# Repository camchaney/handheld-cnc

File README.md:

## Description
Compass is a DIY handheld CNC router designed to make CNC machining more accessible.

Unlike traditional CNC machines that move a cutting tool within a fixed workspace, Compass relies on users to guide the device around the workpiece directly. It automatically adjusts the cutting tool to stay on the programmed design path, enabling a significantly smaller device footprint while still handling large-scale cuts.

This is all accomplished using optical flow mouse sensors to track the position of the device, as well as a belt driven coreXY gantry to adjust the tool. The brains are a Teensy 4.1 microcontroller.

## Getting Started
This repo contains all of the source to build a Handheld CNC Router: the firmware, CAD files for 3D printing/manufacturing, BOM, and cable diagrams.

### Navigation
Internal
- [main](main/) - main firmware (written for [PlatformIO](https://docs.platformio.org/en/latest/core/quickstart.html) usage)
- [cad](cad/) - custom hardware (3D prints, laser cut sheet metal, cable harnesses)
- [pcb](pcb/) - printed circuit board designs for motherboard and sensors
- [dev](dev/) - development folder for debugging and testing
- [examples](examples/) - example gcode files to test with your machine!

External
- [BOM](https://docs.google.com/spreadsheets/d/12QS1CGSAB-lqKIOotCXDaXmJv9cjfRvVEAgQbRd7MnY/edit?usp=sharing)
- [Assembly Instructions](https://drive.google.com/drive/folders/1fIALrTWUbJRqTl93RGrUaR8dMfO7AI_g?usp=sharing)

## Disclaimer
This project is a work-in-progress. Development is rapidly occurring, so design files and firmware may change.

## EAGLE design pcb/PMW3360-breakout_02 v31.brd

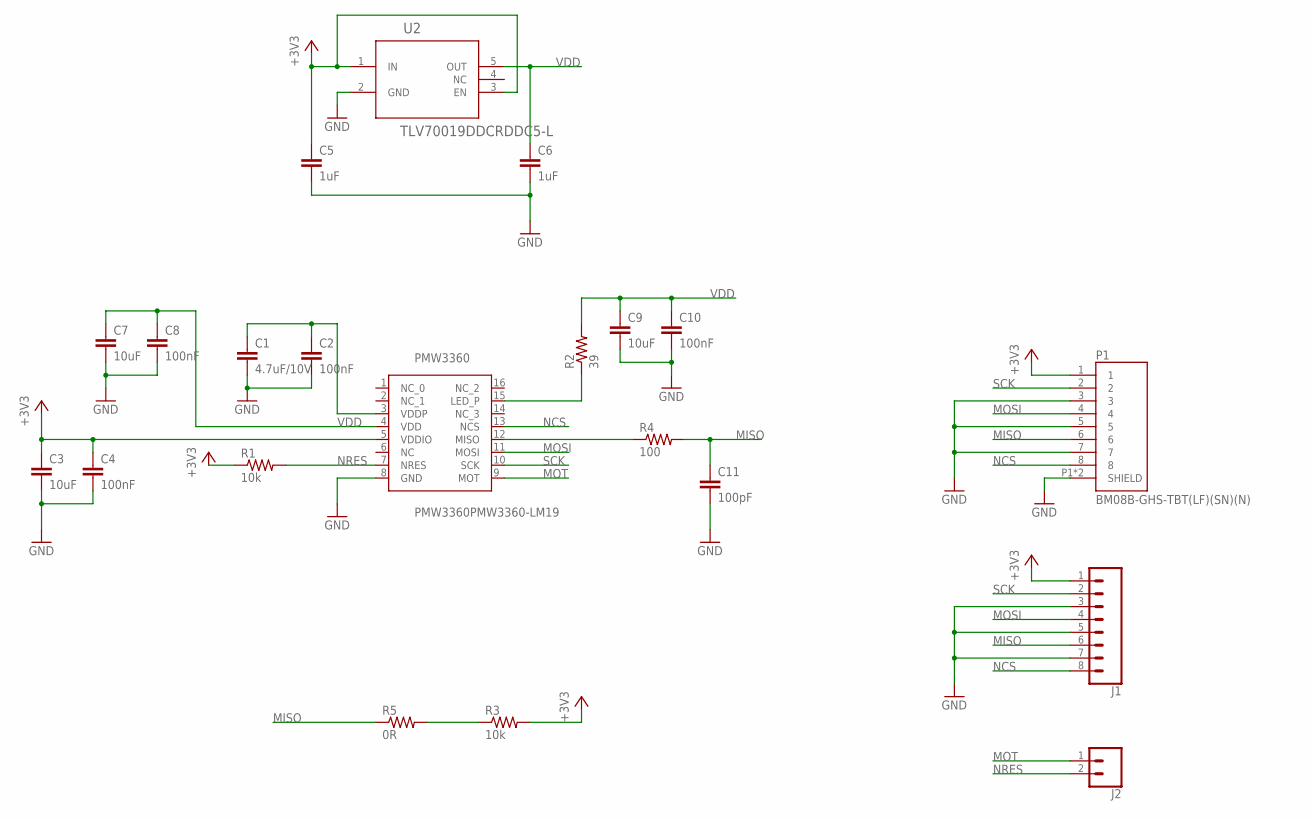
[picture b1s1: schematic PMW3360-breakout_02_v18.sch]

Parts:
C1: 4.7uF/10V; CAPC1608X85
C2, C4, C8, C10: 100nF; CAPC1005X60
C3, C7, C9: 10uF; CAPC1005X60
C5, C6: 1uF; CAPC1005X60
C11: 100pF; C0402K
J1: CONN_08"; 1X08
J2: CONN_02; 1X02
P1: BM08B-GHS-TBT(LF)(SN)(N); JST_BM08B-GHS-TBT(LF)(SN)(N)
PMW3360: PMW3360PMW3360-LM19; PMW3360
R1, R3: 10k; R0402
R2: 39; R0402
R4: 100; R0402
R5: 0R; R0402
U2: TLV70019DDCRDDC5-L; DDC5-L

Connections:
+3V3: C3.1, C4.1, C5.1, J1.1, P1.1, PMW3360.5 (VDDIO), R1.1, R3.2, U2.1 (IN), U2.3 (EN)
GND: C1.2, C2.2, C3.2, C4.2, C5.2, C6.2, C7.2, C8.2, C9.2, C10.2, C11.2, J1.3, J1.5, J1.7, P1.3, P1.5, P1.7, P1.P1 (SHIELD), P1.P2 (SHIELD), PMW3360.8 (GND), U2.2 (GND)
MISO: C11.1, J1.6, P1.6, R4.2, R5.1
MOSI: J1.4, P1.4, PMW3360.11 (MOSI)
MOT: J2.1, PMW3360.9 (MOT)
unnamed: PMW3360.15 (LED_P), R2.1
unnamed: C1.1, C2.1, PMW3360.3 (VDDP)
unnamed: PMW3360.12 (MISO), R4.1
unnamed: R3.1, R5.2
NCS: J1.8, P1.8, PMW3360.13 (NCS)
NRES: J2.2, PMW3360.7 (NRES), R1.2
SCK: J1.2, P1.2, PMW3360.10 (SCK)
VDD: C6.1, C7.1, C8.1, C9.1, C10.1, PMW3360.4 (VDD), R2.2, U2.5 (OUT)

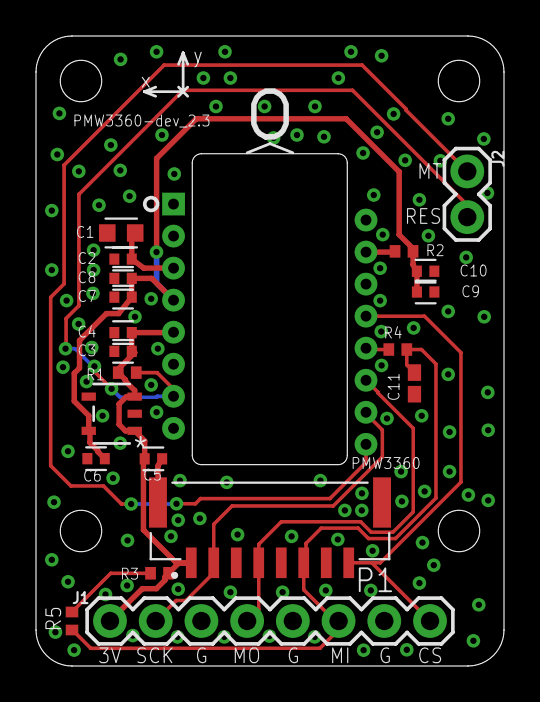
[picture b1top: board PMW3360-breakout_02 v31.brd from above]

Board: 2 copper layers, 26.0 x 35.0 mm, 21 parts (0 on the bottom side), 13 nets.

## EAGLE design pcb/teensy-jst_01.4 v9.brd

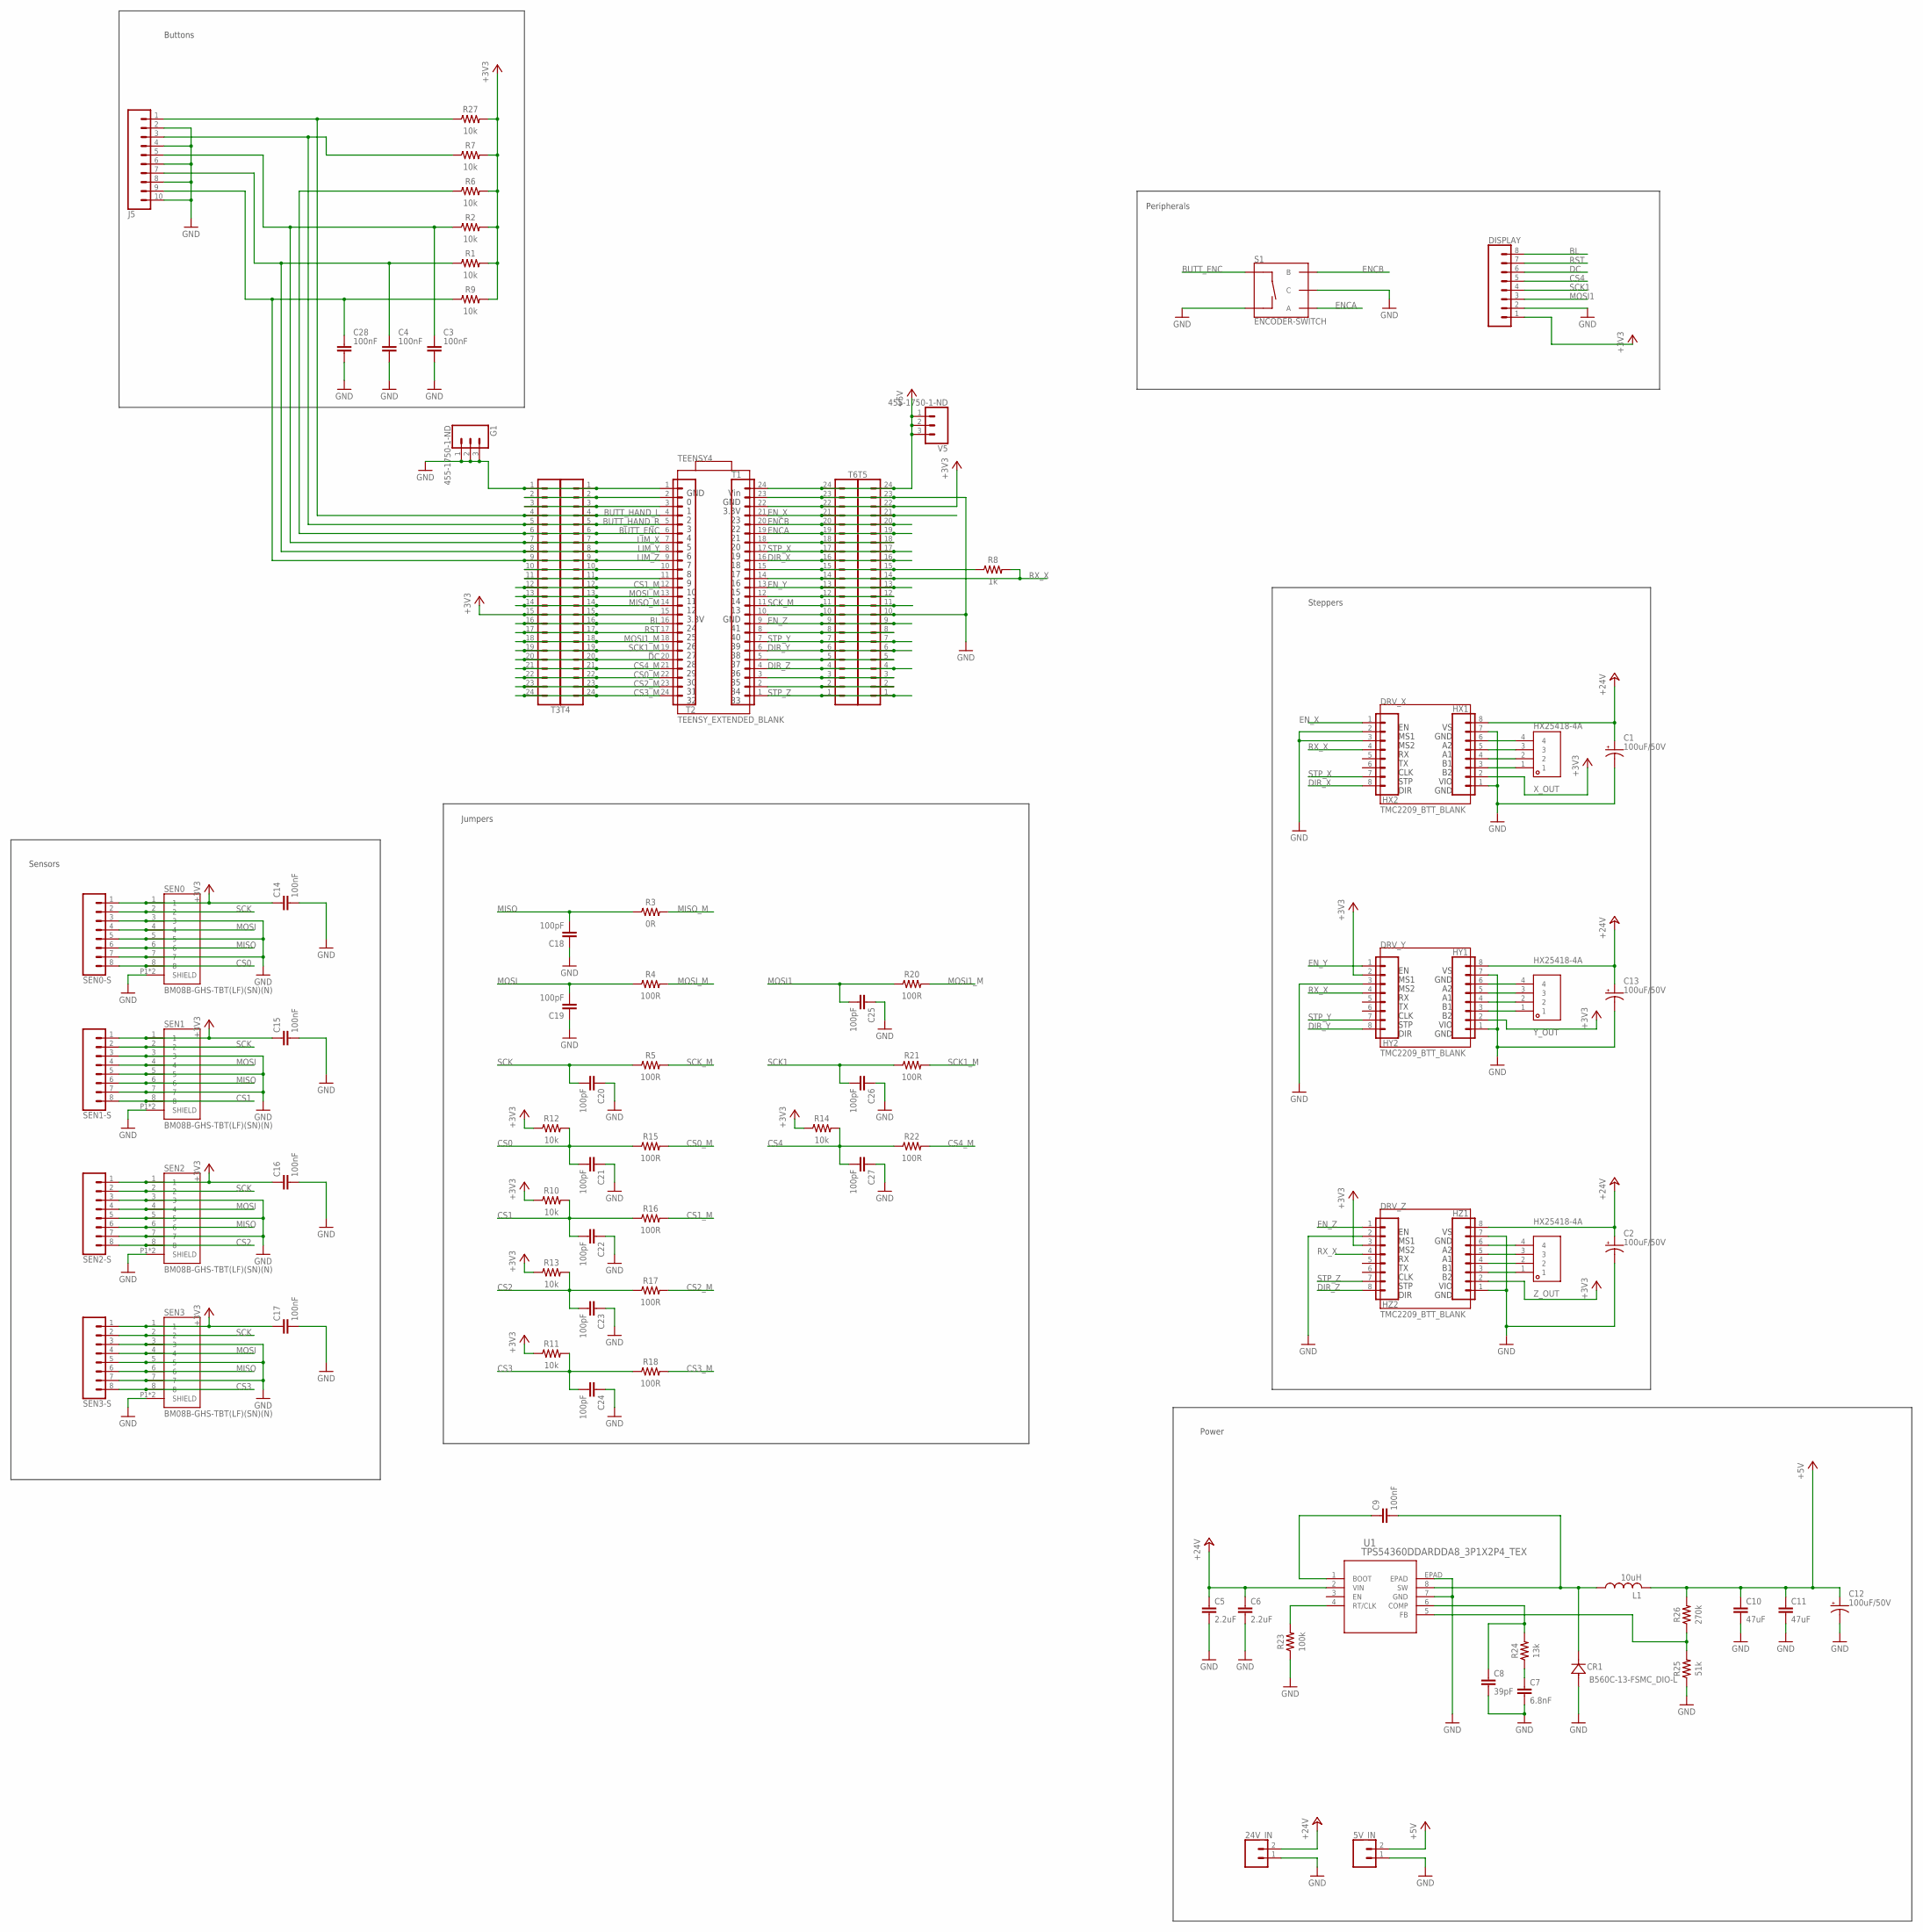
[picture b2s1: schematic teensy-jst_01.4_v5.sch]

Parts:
5V_IN, 24V_IN: CONN_025MM; SCREWTERMINAL-5MM-2
C1, C2, C12, C13: 100uF/50V; PANASONIC_D
C3, C4, C28: 100nF; C0603
C5, C6: 2.2uF; C0603
C7: 6.8nF; C0603
C8: 39pF; C0402
C9, C14, C15, C16, C17: 100nF; C0402
C10, C11: 47uF; C0805
C18, C19, C20, C21, C23, C24, C25, C26, C27: 100pF; C0402K
C22: 100pF; C0402
CR1: B560C-13-FSMC_DIO-L; SMC_DIO-L
DISPLAY: CONN_08"; 1X08
DRV_X: TMC2209_BTT_BLANK; MODULE_TMC2209_BTT_BLANK
DRV_Y: TMC2209_BTT_BLANK; MODULE_TMC2209_BTT_BLANK
DRV_Z: TMC2209_BTT_BLANK; MODULE_TMC2209_BTT_BLANK
G1: 455-1750-1-ND; 1X03
HX1, HX2: CONN_08"; 1X08
HY1, HY2: CONN_08"; 1X08
HZ1, HZ2: CONN_08"; 1X08
J5: CONN_10"; 1X10
L1: 10uH; MWSA0503S-100MT
R1, R2, R6, R7, R9, R10, R11, R12, R13, R14, R27: 10k; RESC1608X60
R3: 0R; RESC1608X60
R4, R5, R15, R16, R17, R18, R20, R21, R22: 100R; RESC1608X60
R8: 1k; RESC1608X60
R23: 100k; RESC1005X40
R24: 13k; RESC1608X60
R25: 51k; RESC1608X60
R26: 270k; RESC1005X40
S1: ENCODER-SWITCH; ROTARY_ENC_PLAIN
SEN0, SEN1, SEN2, SEN3: BM08B-GHS-TBT(LF)(SN)(N); JST_BM08B-GHS-TBT(LF)(SN)(N)
SEN0-S, SEN1-S, SEN2-S, SEN3-S: CONN_08"; 1X08
T1, T2, T3, T4, T5, T6: CONN_24; 1X24
TEENSY4: TEENSY_EXTENDED_BLANK
U1: TPS54360DDARDDA8_3P1X2P4_TEX; DDA8_3P1X2P4_TEX
V5: 455-1750-1-ND; 1X03
X_OUT: HX25418-4A
Y_OUT: HX25418-4A
Z_OUT: HX25418-4A

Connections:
+3V3: C14.1, C15.1, C16.1, C17.1, DISPLAY.1, HX1.2, HY1.2, HY2.2, HZ1.2, HZ2.3, R1.2, R2.2, R6.2, R7.2, R9.2, R10.1, R11.1, R12.1, R13.1, R14.1, R27.2, SEN0.1, SEN0-S.1, SEN1.1, SEN1-S.1, SEN2.1, SEN2-S.1, SEN3.1, SEN3-S.1, T1.22, T2.15, T3.15, T4.15, T5.22, T6.22
+5V: 5V_IN.2, C10.1, C11.1, C12.+, L1.2, R26.2, T1.24, T5.24, T6.24, V5.1, V5.2, V5.3
+24V: 24V_IN.2, C1.+, C2.+, C5.1, C6.1, C13.+, HX1.8, HY1.8, HZ1.8, U1.2 (VIN)
BL: DISPLAY.8, T2.16, T3.16, T4.16
BUTT_ENC: R6.1, S1.SW+, T2.6, T3.6, T4.6
BUTT_HAND_L: J5.1, R27.1, T2.4, T3.4, T4.4
BUTT_HAND_R: J5.3, R7.1, T2.5, T3.5, T4.5
CS0: C21.2, R12.2, R15.1, SEN0.8, SEN0-S.8
CS0_M: R15.2, T2.22, T3.22, T4.22
CS1: C22.2, R10.2, R16.1, SEN1.8, SEN1-S.8
CS1_M: R16.2, T2.12, T3.12, T4.12
CS2: C23.2, R13.2, R17.1, SEN2.8, SEN2-S.8
CS2_M: R17.2, T2.23, T3.23, T4.23
CS3: C24.2, R11.2, R18.1, SEN3.8, SEN3-S.8
CS3_M: R18.2, T2.24, T3.24, T4.24
CS4: C27.2, DISPLAY.5, R14.2, R22.1
CS4_M: R22.2, T2.21, T3.21, T4.21
DC: DISPLAY.6, T2.20, T3.20, T4.20
DIR_X: HX2.8, T1.16, T5.16, T6.16
DIR_Y: HY2.8, T1.6, T5.6, T6.6
DIR_Z: HZ2.8, T1.4, T5.4, T6.4
ENCA: S1.A, T1.19, T5.19, T6.19
ENCB: S1.B, T1.20, T5.20, T6.20
EN_X: HX2.1, T1.21, T5.21, T6.21
EN_Y: HY2.1, T1.13, T5.13, T6.13
EN_Z: HZ2.1, T1.9, T5.9, T6.9
GND: 5V_IN.1, 24V_IN.1, C1.-, C2.-, C3.2, C4.2, C5.2, C6.2, C7.2, C8.2, C10.2, C11.2, C12.-, C13.-, C14.2, C15.2, C16.2, C17.2, C18.1, C19.1, C20.1, C21.1, C22.1, C23.1, C24.1, C25.1, C26.1, C27.1, C28.2, CR1.2, DISPLAY.2, G1.1, G1.2, G1.3, HX1.1, HX1.7, HX2.2, HX2.3, HY1.1, HY1.7, HY2.3, HZ1.1, HZ1.7, HZ2.2, J5.2, J5.4, J5.6, J5.8, J5.10, R23.1, R25.1, S1.C, S1.SW-, SEN0.3, SEN0.5, SEN0.7, SEN0.P1 (SHIELD), SEN0.P2 (SHIELD), SEN0-S.3, SEN0-S.5, SEN0-S.7, SEN1.3, SEN1.5, SEN1.7, SEN1.P1 (SHIELD), SEN1.P2 (SHIELD), SEN1-S.3, SEN1-S.5, SEN1-S.7, SEN2.3, SEN2.5, SEN2.7, SEN2.P1 (SHIELD), SEN2.P2 (SHIELD), SEN2-S.3, SEN2-S.5, SEN2-S.7, SEN3.3, SEN3.5, SEN3.7, SEN3.P1 (SHIELD), SEN3.P2 (SHIELD), SEN3-S.3, SEN3-S.5, SEN3-S.7, T1.10, T1.23, T2.1, T3.1, T4.1, T5.10, T5.23, T6.10, T6.23, U1.7 (GND), U1.EPAD
LIM_X: C3.1, J5.5, R2.1, T2.7, T3.7, T4.7
LIM_Y: C4.1, J5.7, R1.1, T2.8, T3.8, T4.8
LIM_Z: C28.1, J5.9, R9.1, T2.9, T3.9, T4.9
MISO: C18.2, R3.1, SEN0.6, SEN0-S.6, SEN1.6, SEN1-S.6, SEN2.6, SEN2-S.6, SEN3.6, SEN3-S.6
MISO_M: R3.2, T2.14, T3.14, T4.14
MOSI: C19.2, R4.1, SEN0.4, SEN0-S.4, SEN1.4, SEN1-S.4, SEN2.4, SEN2-S.4, SEN3.4, SEN3-S.4
MOSI1: C25.2, DISPLAY.3, R20.1
MOSI1_M: R20.2, T2.18, T3.18, T4.18
MOSI_M: R4.2, T2.13, T3.13, T4.13
unnamed: T2.2, T3.2, T4.2
unnamed: T2.3, T3.3, T4.3
unnamed: T2.10, T3.10, T4.10
unnamed: T2.11, T3.11, T4.11
unnamed: R23.2, U1.4 (RT/CLK)
unnamed: T1.12, T5.12, T6.12
unnamed: C7.1, R24.1
unnamed: T1.3, T5.3, T6.3
unnamed: HZ1.6, Z_OUT.4
unnamed: T1.2, T5.2, T6.2
unnamed: C8.1, R24.2, U1.6 (COMP)
unnamed: HZ1.5, Z_OUT.3
unnamed: T1.8, T5.8, T6.8
unnamed: HX1.6, X_OUT.4
unnamed: HX1.5, X_OUT.3
unnamed: R25.2, R26.1, U1.5 (FB)
unnamed: HZ1.4, Z_OUT.2
unnamed: HZ1.3, Z_OUT.1
unnamed: T1.18, T5.18, T6.18
unnamed: HY1.4, Y_OUT.2
unnamed: HX1.4, X_OUT.2
unnamed: HX1.3, X_OUT.1
unnamed: T1.5, T5.5, T6.5
unnamed: R8.1, T1.15, T5.15, T6.15
unnamed: HY1.3, Y_OUT.1
unnamed: C9.2, CR1.1, L1.1, U1.8 (SW)
unnamed: C9.1, U1.1 (BOOT)
unnamed: HY1.6, Y_OUT.4
unnamed: HY1.5, Y_OUT.3
RST: DISPLAY.7, T2.17, T3.17, T4.17
RX_X: HX2.4, HY2.4, HZ2.4, R8.2, T1.14, T5.14, T6.14
SCK: C20.2, R5.1, SEN0.2, SEN0-S.2, SEN1.2, SEN1-S.2, SEN2.2, SEN2-S.2, SEN3.2, SEN3-S.2
SCK1: C26.2, DISPLAY.4, R21.1
SCK1_M: R21.2, T2.19, T3.19, T4.19
SCK_M: R5.2, T1.11, T5.11, T6.11
STP_X: HX2.7, T1.17, T5.17, T6.17
STP_Y: HY2.7, T1.7, T5.7, T6.7
STP_Z: HZ2.7, T1.1, T5.1, T6.1

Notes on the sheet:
Jumpers
Peripherals
Steppers
Sensors
Power
Buttons

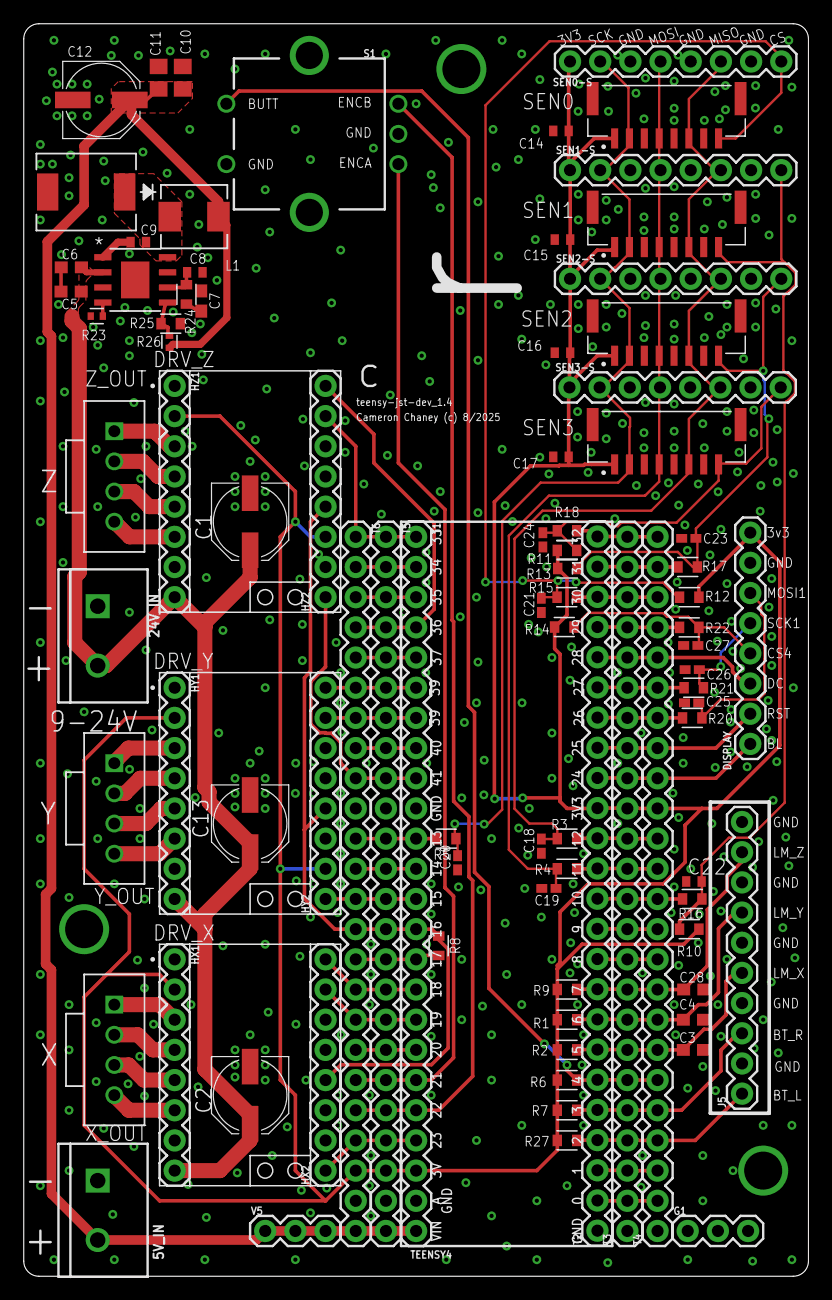
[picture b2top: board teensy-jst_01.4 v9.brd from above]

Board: 2 copper layers, 66.0 x 105.4 mm, 91 parts (0 on the bottom side), 74 nets.

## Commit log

2023-12-24 ignoring pot for now
2023-12-30 implementing threshold based sensor filtering
2024-12-09 grouping dataframes into dicts
2024-12-09 fixed angle plotting and adding rotation
2024-12-09 fixing rotation
2024-12-11 path sorting dev and class refactor
2024-12-11 reorganize
2024-12-14 reformatting and deleting unecessary stuff
2025-08-04 Add USB storage support and update file handling for SD and USB volumes
2025-08-04 Add USBHost_t36 library for USB support
2025-08-11 Implement USB storage support flag
2025-08-11 Implement Auto Touch
2025-08-11 Rename isPressed to arePressed for clarity in HandleButtons class
2025-08-11 test stuff
2025-08-12 Implement interrupt-based stepping for Z-axis motor control
2025-08-12 Implement auto touch functionality for Z-axis and enhance button handling
2025-08-12 Update auto touch retraction value in motors and add constant for retraction compensation
2025-08-12 Refactor include statement for TimerOne library in motors.cpp
2025-08-18 Add menu management framework
2025-08-19 Enhance Compass UI: Implement acceleration for encoder adjustments and add double-click functionality
2025-08-19 Implement confirm dialog to CompassUI Replaced matThickness with deepth Add Draw gCode Setting to set x < 0 ito 0 in gocde files
2025-08-19 Refactor path generation: Remove tilt variable and adjust path calculations to incorporate xOffset, yOffset, and rotation
2025-08-19 Implement old fileSelector
2025-08-19 Remove redundant call to workspaceZeroXY in onStartPresetCut function
2025-08-19 Add file cut to new menu
2025-08-19 fix small changes
2025-08-19 Implement stop Ask for claibration start
2025-08-19 Add cutting menu actions and refactor cutting functions
    - Implement onStartRezeroXY and onStartCancelCut functions.
    - Replace stop cutting action with cancel cutting in the menu.
    - Introduce speed run submenu and associated action.
    - Refactor startCutting function to streamline cutting process.
2025-08-19 Fix screen initialization parameter for Arduino_GFX
2025-08-20 Refactor circleGenerator to remove unnecessary offsets in point calculations
2025-08-20 Refactor UI components and remove unused display code
2025-08-20 Add persistent settings
2025-08-20 Fix line generator
2025-08-21 fix center of circle
2025-08-21 Fix parking position after cut #20
2025-08-21 draw eveything z< 0 with 0 #22
2025-09-07 mark DNS 100pF capacitors as DNS and 0pF so that no one else makes the stupid mistake I did
2025-10-22 live gcode dev
2025-10-22 live gcode working for preset designs
    It is still buggy. If increasing the speed, the buffer won't be able to keep up
2025-10-23 very buggy, but some progress
    The buffer isn't working super well for sd reading. I think it has something to do with how the currentFilePosition is being updated. It should be updated so that the file starts seeking from the cur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
2025-10-29 couple little fixes
2025-10-30 adding faceplate stl file
2025-10-31 fixing incomplete z home bug and clarifying end
    The screen now gives directions for how to "accept" or "cancel" an auto z homing. Also fixed a bug where an incomplete z homing would be accepted
2025-10-31 little refactor
2025-10-31 updating old readme :/
    Updated the description of the gantry system used in the device.
2025-11-11 adding fusion CAD source file
2025-11-12 Refactor floating-point literals to use 'f' suffix for consistency
    - Updated various floating-point literals across multiple files to include the 'f' suffix for clarity and to ensure they are treated as float types.
    - Adjusted mathematical functions to use their float variants (e.g., sqrtf, powf, sinf) for improved performance and type safety.
2025-11-13 use ISR instead of polling Use DMA for reading SPI for really crasy perforance
2025-11-13 refactor sensor timer ISR for improved data handling
2025-11-14 interrupts not working properly
    This still needs some work. It compiles, but the interrupts are not working properly. I think the doSensing function is way to cumbersome for an ISR. This is mainly due to the 4x calls to readBurst, 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

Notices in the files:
parts and their libraries:
SparkFun-Connectors: Licensing: Creative Commons ShareAlike 4.0 International - https://creativecommons.org/licenses/by-sa/4.0
COPYRIGHT: Copyright (C) 2024 Ultra Librarian. All rights reserved.
